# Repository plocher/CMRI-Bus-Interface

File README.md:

# CMRI-Bus-Interface
## License: CERN Open Hardware Licence v1.2

RS422/485 driver for CMRI-Net

Daughter board for interfacing with CMRI Bus traffic using MRCS 'duino example code.
Uses an optional onboard 555 to generate TX/RX enable based on processor I/O direction

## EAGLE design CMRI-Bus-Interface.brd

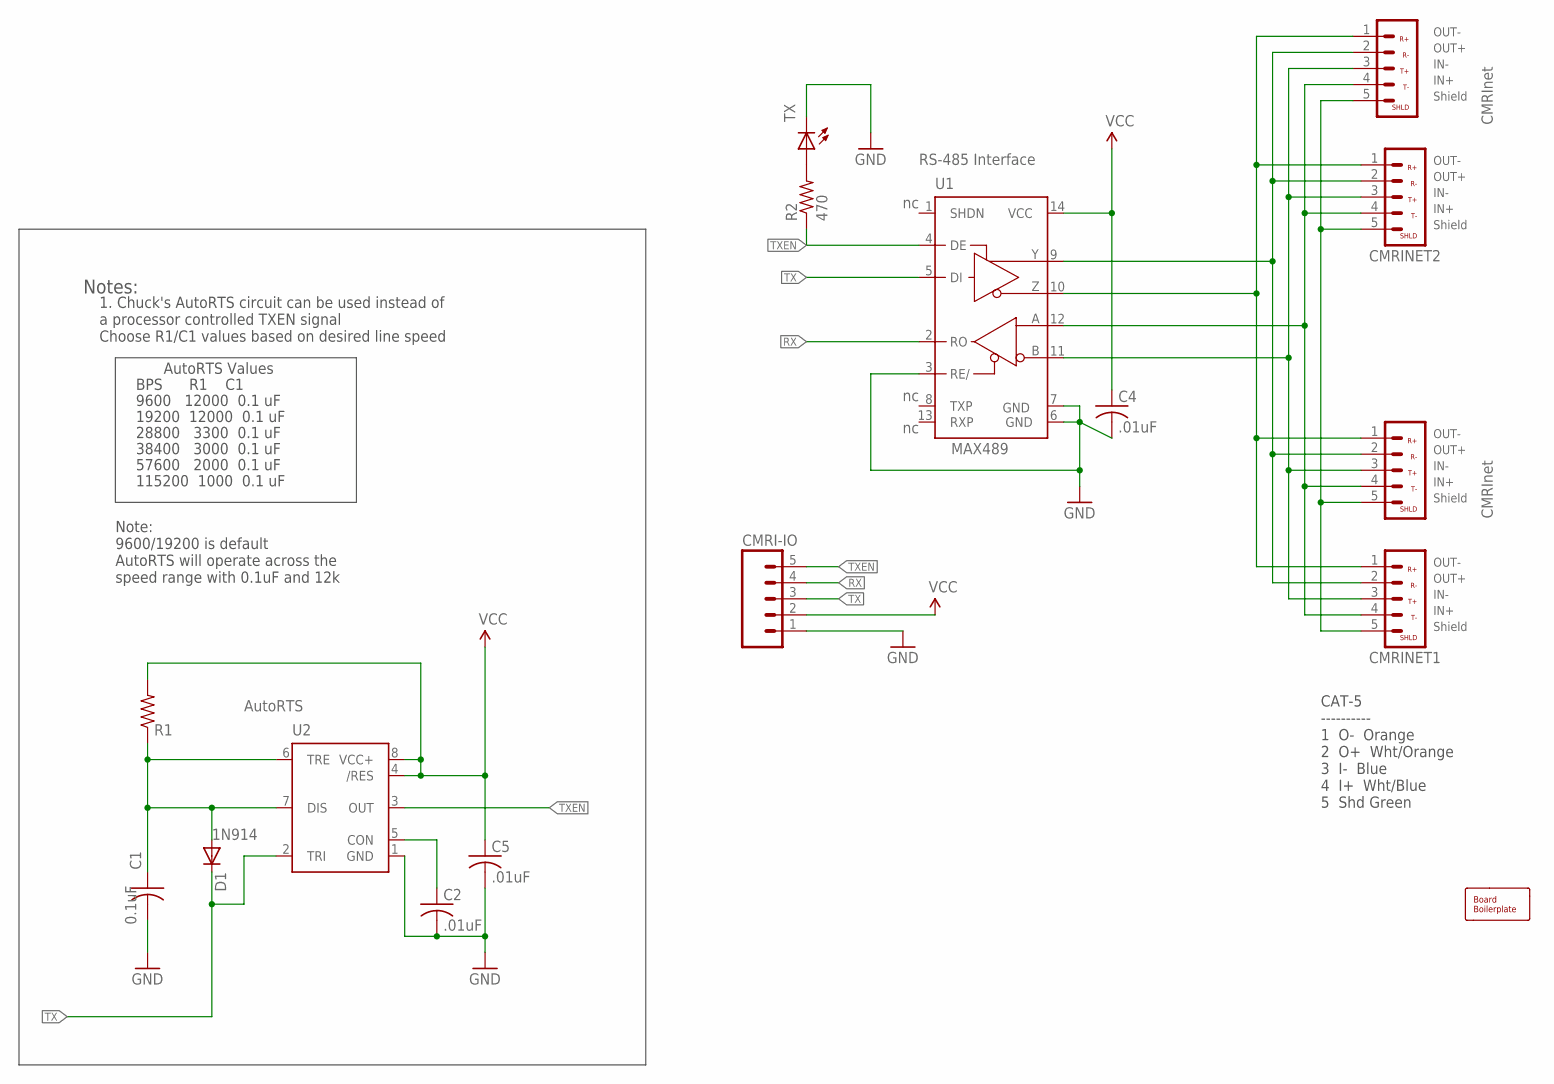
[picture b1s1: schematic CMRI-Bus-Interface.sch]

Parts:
BOARD1: BOARD69X70; BOARD-DINRAIL-2.7IN-7CM
C1: 0.1uF; C050-024X044
C2: .01uF; C050-024X044
C4, C5: .01uF; C-PTH-0.100
CMRI-IO: CONNECTOR-M05CMRI; CON-CMRI-IO
CMRINET1, CMRINET2: CMRInet; CMRINET-3.5MM
CMRINET3, CMRINET4: CMRInet; KK-156-5
D1: 1N4148; DIODE-1N4148
R1: RPTH03; AXIAL-0.3-RES
R2: 470; AXIAL-0.3-RES
TX: LEDLED5MM; LED5MM
U1: MAX3465CPD; DIL14
U2: NE555P; DIL-08

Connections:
GND: C1.2, C2.2, C4.2, C5.2, CMRI-IO.1, TX.K (C), U1.3 (RE/), U1.6 (GND), U1.7 (GND), U2.1 (GND)
IN+: CMRINET1.4, CMRINET2.4, CMRINET3.4, CMRINET4.4, U1.12 (A)
IN-: CMRINET1.3, CMRINET2.3, CMRINET3.3, CMRINET4.3, U1.11 (B)
unnamed: R2.P$2 (2), TX.A
unnamed: C2.1, U2.5 (CON)
unnamed: C1.1, D1.A, R1.P$1 (1), U2.6 (TRE), U2.7 (DIS)
OUT+: CMRINET1.2, CMRINET2.2, CMRINET3.2, CMRINET4.2, U1.9 (Y)
OUT-: CMRINET1.1, CMRINET2.1, CMRINET3.1, CMRINET4.1, U1.10 (Z)
RX: CMRI-IO.4, U1.2 (RO)
SHIELD: CMRINET1.5, CMRINET2.5, CMRINET3.5, CMRINET4.5
TX: CMRI-IO.3, D1.C, U1.5 (DI), U2.2 (TRI)
TXEN: CMRI-IO.5, R2.P$1 (1), U1.4 (DE), U2.3 (OUT)
VCC: C4.1, C5.1, CMRI-IO.2, R1.P$2 (2), U1.14 (VCC), U2.4 (/RES), U2.8 (VCC+)

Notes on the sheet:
IN+
IN-
OUT+
OUT-
1N914
MAX489
RS-485 Interface
Notes:
1. Chuck's AutoRTS circuit can be used instead of a processor controlled TXEN signal Choose R1/C1 values based on desired line speed
AutoRTS
Shield
AutoRTS Values
9600 12000 0.1 uF
19200 12000 0.1 uF
38400 3000 0.1 uF
57600 2000 0.1 uF
115200 1000 0.1 uF
BPS R1 C1
CAT-5 ---------- 1 O- Orange 2 O+ Wht/Orange 3 I- Blue 4 I+ Wht/Blue 5 Shd Green
28800 3300 0.1 uF
Note: 9600/19200 is default AutoRTS will operate across the speed range with 0.1uF and 12k

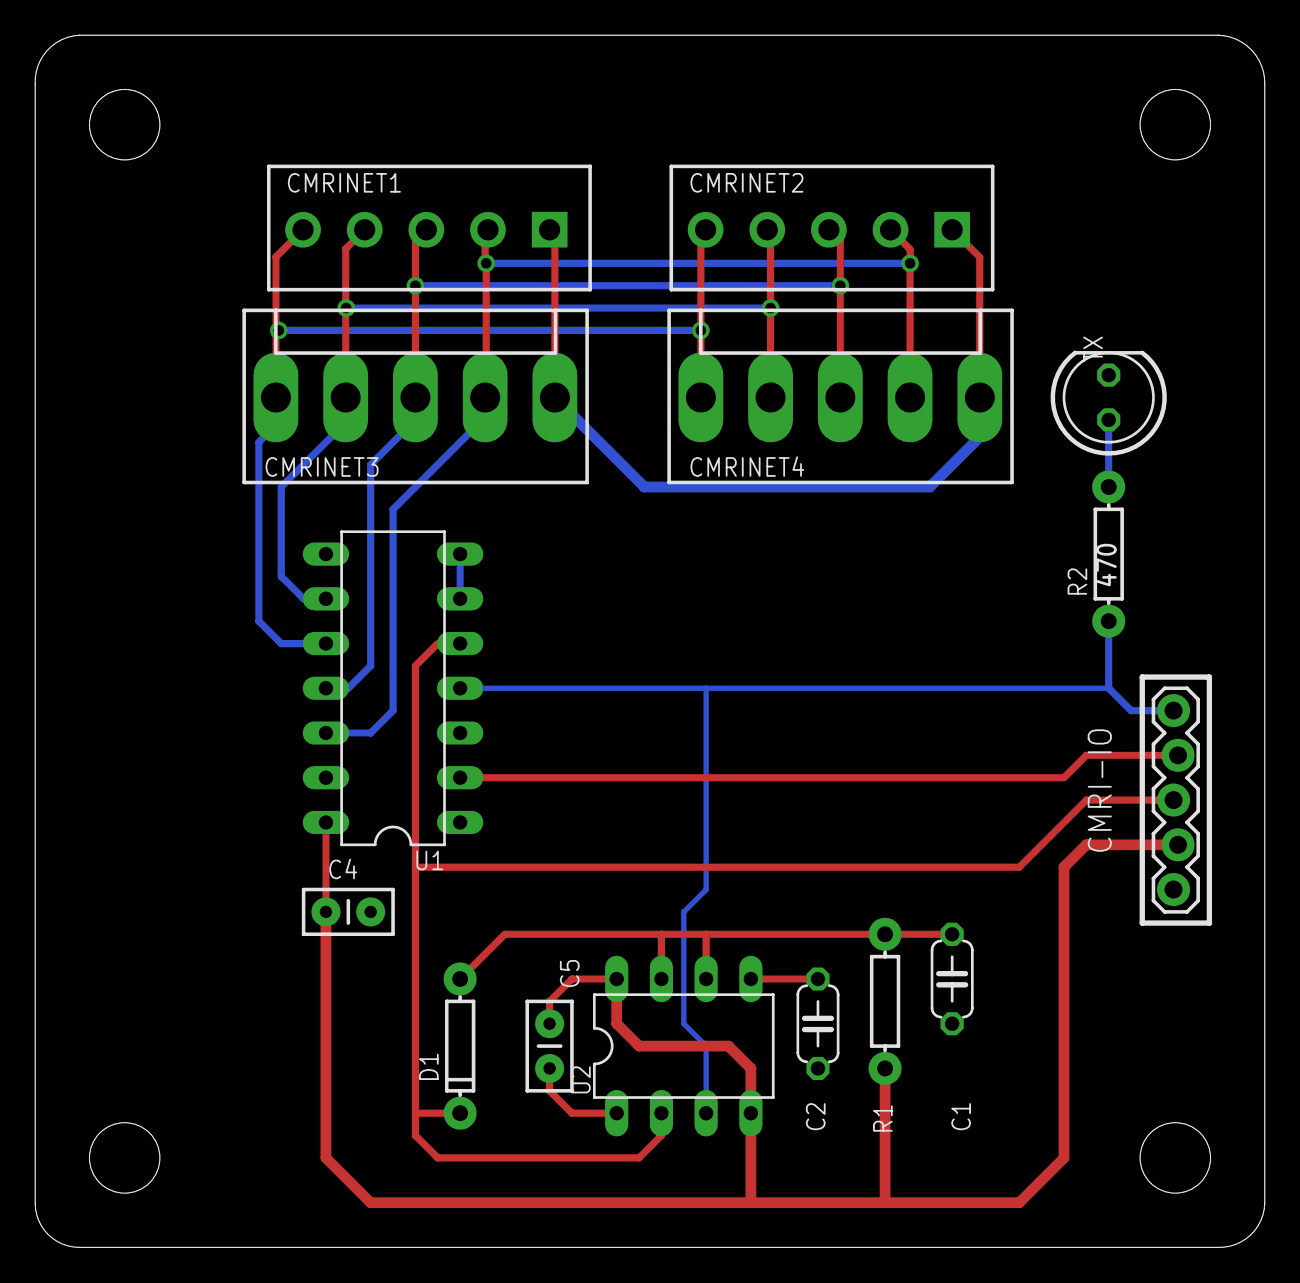
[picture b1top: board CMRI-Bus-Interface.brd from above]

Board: 2 copper layers, 69.8 x 68.8 mm, 17 parts (0 on the bottom side), 13 nets.

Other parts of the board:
U$3: MRCS-LOGO

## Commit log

2019-12-09 added graphic
2020-01-22 TXEN and RX were shorted
2020-05-04 updated tags
2020-09-19 Obsolete
